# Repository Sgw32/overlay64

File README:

overlay64 - video overlay module

!!!SMD version!!!

This SMD version has reduced cost of manufacturing, since DIP Atmegas are rare and expensive. 
Also changed THD resistors to SMD 0805, suitable for soldering by hand.

The overlay64 module allows superimposing predefined texts onto an
existing composite signal or onto the luminance portion of an s-video
signal depending on the states of up to sixteen digital input
lines. An LM1881 video sync separator IC is used to detect the
vertical and horizontal sync pulses of the video signal. An Atmega1284
uses these signals to synchronize with the video signal and to
superimpose text on the video display by bit-banging the corresponding
characters over SPI.

The user writes a simple configuration file that determines which
texts are to be displayed for which input line states. The
configuration file is converted to a binary format using the supplied
commandline tool before flashing it to the Atmegas's eeprom memory via
the USB interface.

Possible uses include displaying the state of control lines for
additional hardware installed in a homecomputer such as the Commodore
64, for example to display the currently selected kernal based on the
state of the control lines for a multi-kernal adapter.

An early working prototype can be seen in this video where it displays
the runtime configuration of the MixSID Stereo SID board:

https://www.youtube.com/watch?v=0exp2yM0WHM

This repository includes the complete sourcecode of the client
software, the firmware and all design files in KiCAD format.

LICENSING

Hardware licenced under CERN OHL v.1.2, see ./hardware/LICENSE.txt
Software and firmware licenced under GNU GPLv3, see ./LICENSE

The software contains MIT licensed code from
https://github.com/arkku/ihex for reading Intel HEX files, Copyright
(c) 2013-2015 Kimmo Kulovesi, see ./intelhex/LICENSE

The firmware contains the V-USB Driver (https://www.obdev.at/vusb),
(C)2008 Objective Development GmbH.

Distributed in the ./bootloader directory is the USBasp bootloader,
(C)2013 Stephan Baerwolf (matrixstorm@gmx.de) and (C)2008 Objective
Development GmbH (https://www.obdev.at/vusb).

In compliance with the terms of the (identical) V-USB driver and
USBasp bootloader licenses (./firmware/usbdrv/License.txt and
./bootloader/License.txt), the entire project is published under

http://www.henning-bekel.de/overlay64

In addition, this distribution contains

- a circuit diagram in PDF format, see ./hardware/overlay64-schematics.pdf
- the full source code for the host software in ./firmware
- this README file
- references to https://www.obdev.at/vusb

The USB Product and Vendor IDs for the Overlay64 USB device have kindly
been provided by OpenMoko, Inc (http://openmoko.org).

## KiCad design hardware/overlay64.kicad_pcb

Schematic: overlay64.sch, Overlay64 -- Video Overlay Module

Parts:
C1, C4, C5, C6: 100nF; C_Disc_D3_P2.5
C2, C3: 18pF; C_Disc_D3_P2.5
D1, D2: 3.6V; D3
IC1: ATmega1284P-AU; TQFP-44_10x10mm_P0.8mm
J: USB_B_Mini; USB_Mini-B_Lumberg_2486_01_Horizontal
P2: INPUT; Pin_Header_Angled_1x16
P3: CONTROL; Pin_Header_Angled_1x08
P4: MAIN; Pin_Header_Angled_1x03
P5, P6, P7, P8: HOLE; MountingHole_4mm
P9: BYPASS; Pin_Header_Angled_1x16
R1, R2: 68; R3
R3: 1k5; R3
R5: 680k; R3
RV1: 1k; Potentiometer_Bourns_3339P_Angular_ScrewUp
U1: LM1881; DIP-8_W7.62mm
Y1: 20MHz; Crystal_HC49-U_Vertical

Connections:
/BOOT: IC1.9
/C0: IC1.15, P3.8
/C1: IC1.16, P3.7
/C2: IC1.41, P3.6
/C3: IC1.43, P3.5
/C4: IC1.2, P3.4
/C5: IC1.3, P3.3
/C6: IC1.13, P3.2
/C7: IC1.14, P3.1
/D+: D2.1 (K), R2.1; also elsewhere on the board
/D-: D1.1 (K), R1.1, R3.1; also elsewhere on the board
/IN0: IC1.37, P2.16, P9.1
/IN1: IC1.36, P2.15, P9.2
/IN2: IC1.35, P2.14, P9.3
/IN3: IC1.34, P2.13, P9.4
/IN4: IC1.33, P2.12, P9.5
/IN5: IC1.32, P2.11, P9.6
/IN6: IC1.31, P2.10, P9.7
/IN7: IC1.30, P2.9, P9.8
/IN8: IC1.26, P2.8, P9.9
/IN9: IC1.25, P2.7, P9.10
/IN10: IC1.24, P2.6, P9.11
/IN11: IC1.23, P2.5, P9.12
/IN12: IC1.22, P2.4, P9.13
/IN13: IC1.21, P2.3, P9.14
/IN14: IC1.20, P2.2, P9.15
/IN15: IC1.19, P2.1, P9.16
/LUMA: C4.1, P4.2, RV1.3
/MOSI: IC1.1, RV1.2
/~BURST: IC1.42, U1.5
/~HSYNC: IC1.40, U1.1
/~VSYNC: IC1.12, U1.3
unnamed: C2.2, IC1.8, Y1.1
unnamed: C3.2, IC1.7, Y1.2
unnamed: C4.2, U1.2
unnamed: C5.1, R5.1, U1.6
unnamed: IC1.10, R1.2
unnamed: IC1.11, R2.2
VCC: C1.1, C6.1, IC1.5, IC1.17, IC1.27, IC1.38, P4.1, R3.2, U1.8

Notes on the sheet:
Overlay64 video overlay module Copyright 2016 Henning Bekel This documentation describes Open Hardware and is licensed under the CERN OHL v. 1.2. You may redistribute and modify this documentation under the terms of the CERN OHL v.1.2. (http://ohwr.org/cernohl). This documentation is distributed WI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

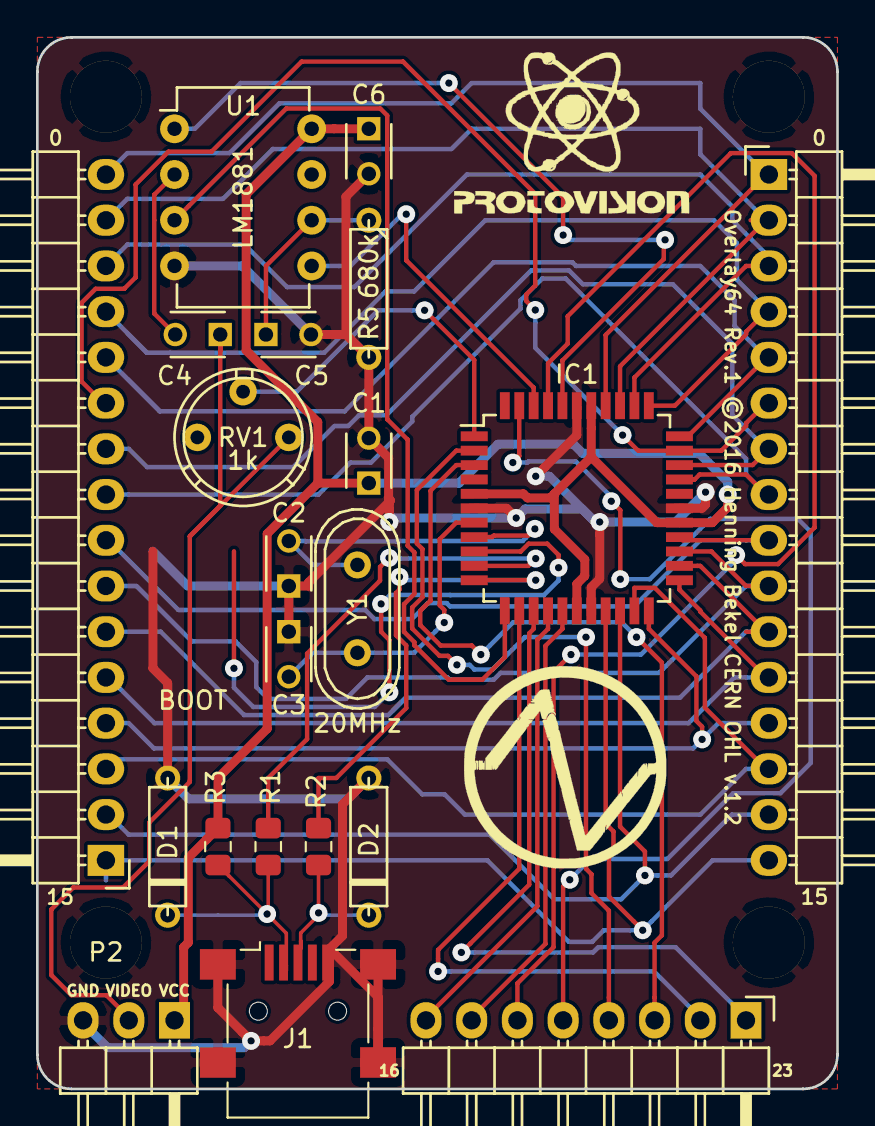
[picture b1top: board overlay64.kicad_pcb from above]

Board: 2 copper layers, 44.5 x 58.4 mm, 25 parts (0 on the bottom side), 39 nets.

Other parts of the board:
J1: USB_B_Mini; USB_Mini-B_Lumberg_2486_01_Horizontal

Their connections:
/D+: J1.3; also elsewhere on the board
/D-: J1.2; also elsewhere on the board

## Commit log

2020-02-02 SMD rework
2020-02-03 Add logos

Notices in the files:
hardware/overlay64.kicad_pcb:
Licensed under CERN OHL v.1.2
Overlay64 Rev.1 ©2016 Henning Bekel CERN OHL v.1.2
